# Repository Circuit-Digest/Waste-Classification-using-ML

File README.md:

# [Waste Classification Using Machine Learning and SCARA Robotic Arm](https://circuitdigest.com/videos/waste-classification-using-machine-learning-and-scara-robotic-arm)

Waste Classification Using Machine Learning and SCARA Robotic Arm
This project introduces an innovative solution to automate waste segregation using a SCARA Robot enhanced with computer vision and machine learning. The project used a pre-deployed AI model to classify the objects into organic or inorganic waste. At its core, the project utilises a Raspberry Pi paired with a USB camera to capture images of waste materials, this captured image is then processed with the help of inference SDK and the Roboflow waste classification API. Once classified, the robotic arm, controlled by an ESP32-C6 WROOM module, handles the waste, placing it into designated bins. This integration of robotics and artificial intelligence not only enhances automation but also contributes to effective waste management solutions.

The SCARA robot retains its compact and precise design, featuring NEMA 17 stepper motors powered by TMC2209 drivers for smooth operation, alongside SG90S servo motors for precise gripper control. The robust power system includes an LM2596-5 buck converter and an ADP7118AUJZ-3.3 LDO, ensuring the reliable operation of the ESP32-C6 and its peripherals. The Raspberry Pi handles image capture, and ML inferencing, leveraging the RoboFlow platform API for real-time inference. A Python-based control script on the Raspberry Pi seamlessly interfaces with the ESP32-C6 via serial communication to coordinate waste classification and robotic arm movements. This project exemplifies the potential of combining robotics and AI to solve real-world challenges. It provides a hands-on platform for exploring automation, embedded systems, and machine learning applications.

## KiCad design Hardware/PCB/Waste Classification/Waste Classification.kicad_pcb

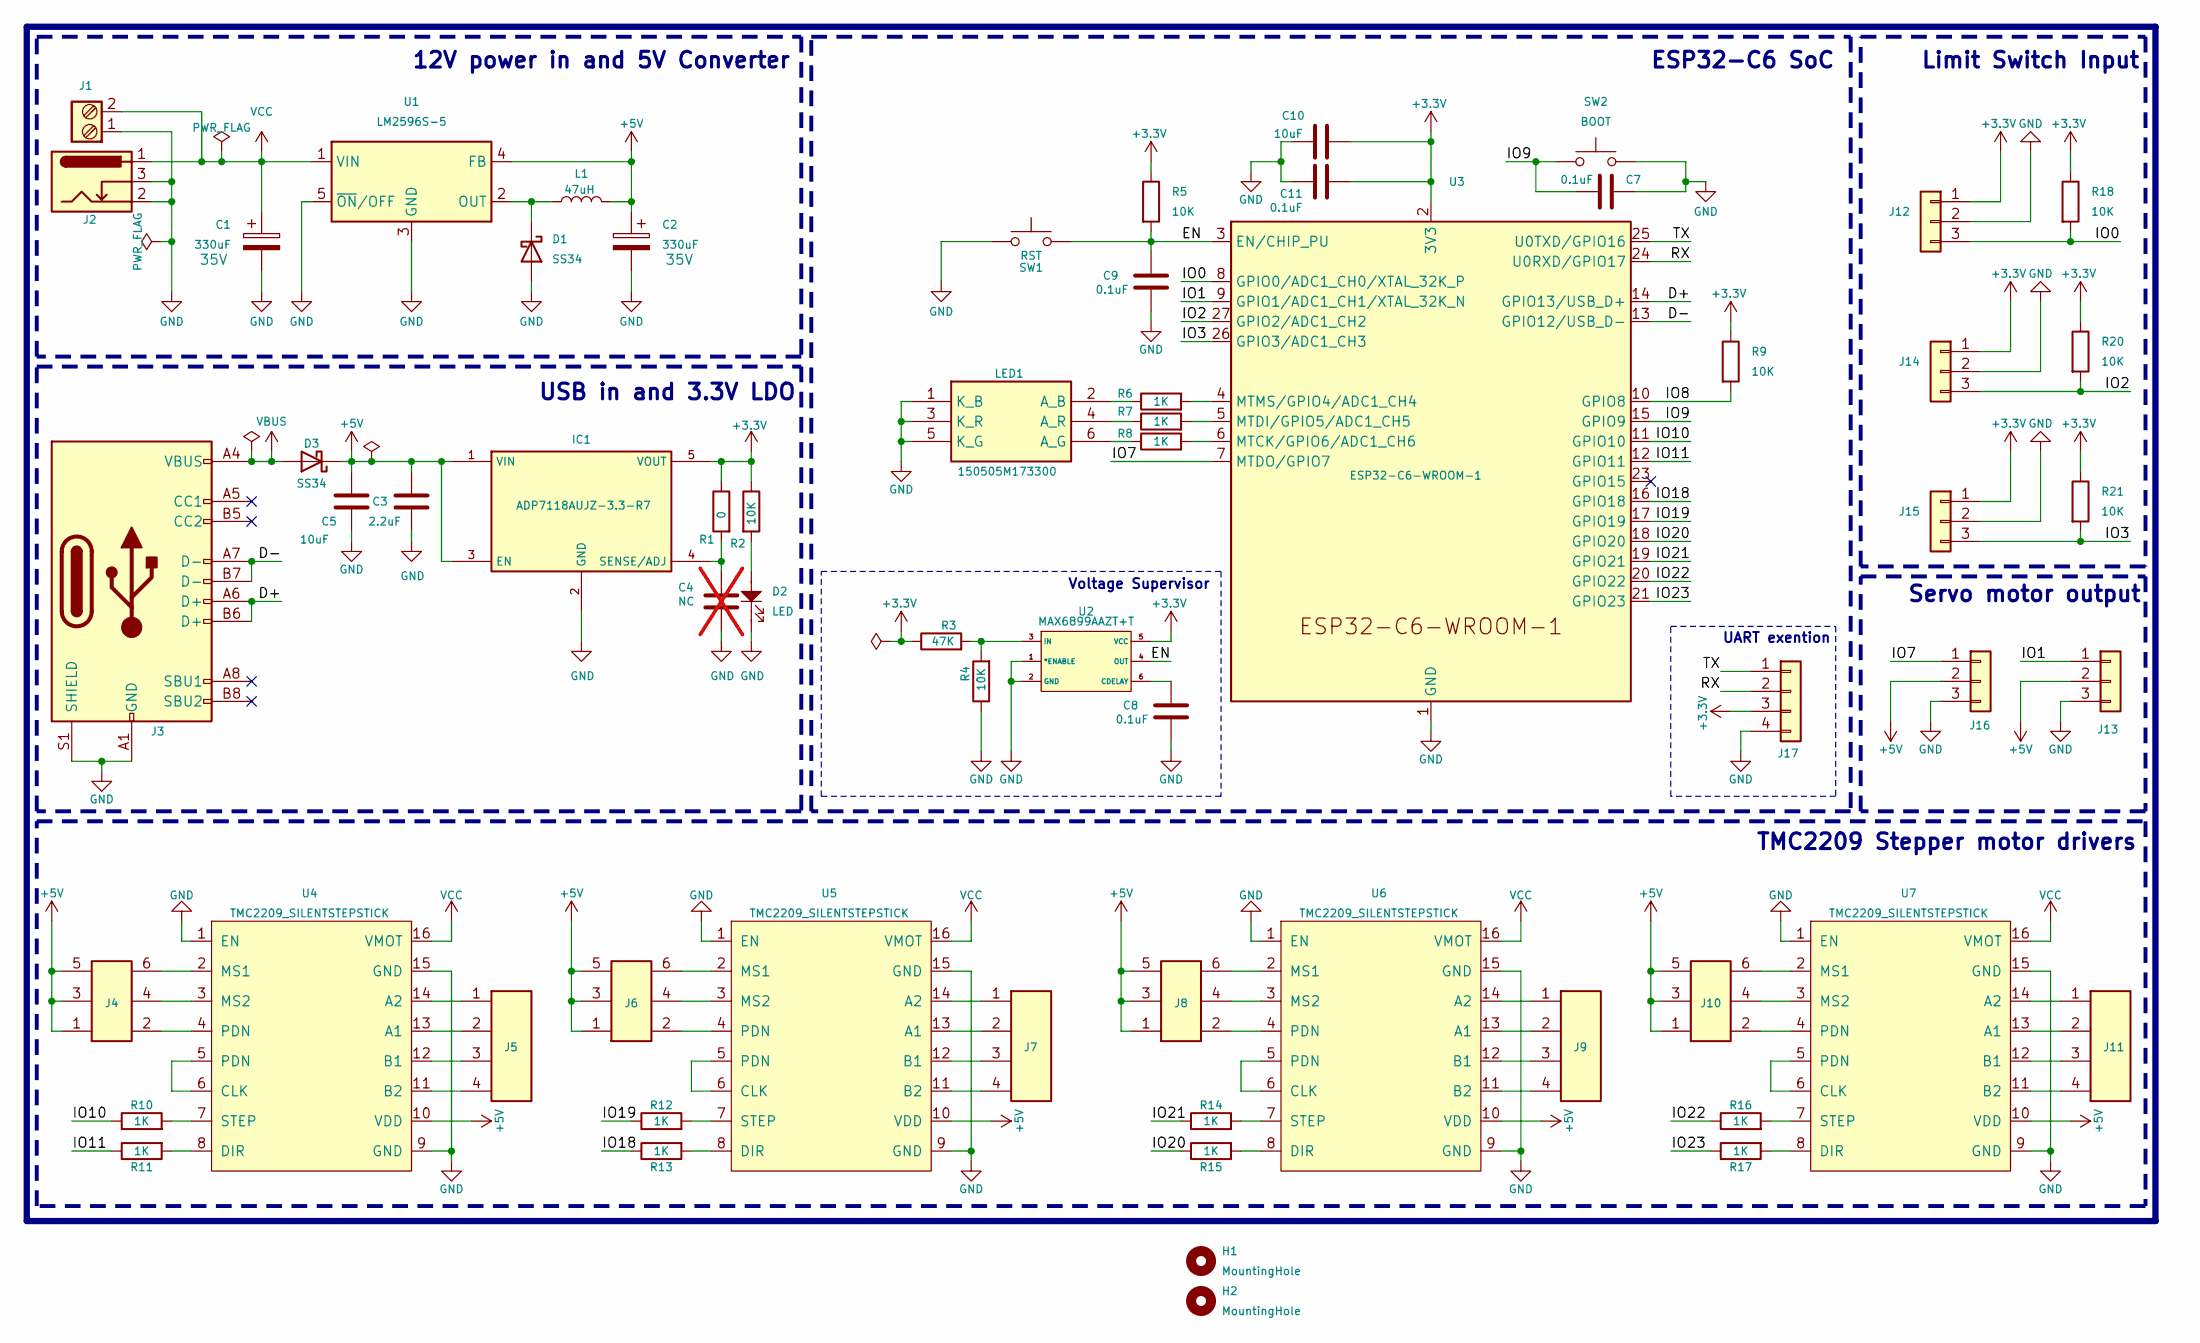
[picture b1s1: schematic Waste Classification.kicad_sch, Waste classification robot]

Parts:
C1, C2: 330uF; CAP_J-V_10X10P5_RUB; Voltage 35V
C3: 2.2uF; C_0603_1608Metric
C4: NC; C_0603_1608Metric; not fitted
C5, C10: 10uF; C_0805_2012Metric
C7, C8, C9, C11: 0.1uF; C_0603_1608Metric
D1, D3: SS34; D_SMA
D2: LED; LED_0805_2012Metric
H1, H2: MountingHole; MountingHole_2.2mm_M2_Pad
IC1: ADP7118AUJZ-3.3-R7; SOT95P280X100-5N; Mouser Part Number 584-ADP7118AUJZ3.3R7
J1: Screw_Terminal_2_P5.00mm; TerminalBlock_Phoenix_PT-1,5-2-5.0-H_1x02_P5.00mm_Horizontal
J2: Barrel_Jack_Switch; BarrelJack_Kycon_KLDX-0202-xC_Horizontal
J3: USB_C_Receptacle_USB2.0; USB_C_Receptacle_HRO_TYPE-C-31-M-12
J4, J6, J8, J10: Conn_02x03_Top_Bottom; PinHeader_2x03_P2.54mm_Vertical
J5, J7, J9, J11: Conn_01x04; JST_XH_B4B-XH-AM_1x04_P2.50mm_Vertical
J12, J13, J14, J15, J16: Conn_01x03; JST_XH_B3B-XH-AM_1x03_P2.50mm_Vertical
J17: Conn_01x04; JST_EH_B4B-EH-A_1x04_P2.50mm_Vertical
L1: 47uH; L_12x12mm_H8mm
LED1: 150505M173300; Mouser Part Number 710-150505M173300
R1: 0; R_0603_1608Metric
R2, R4, R5, R9, R18, R20, R21: 10K; R_0603_1608Metric
R3: 47K; R_0603_1608Metric
R6, R7, R8, R10, R11, R12, R13, R14, R15, R16, R17: 1K; R_0603_1608Metric
SW1: RST; Tactile 3x4x2mm TS-A010
SW2: BOOT; Tactile 3x4x2mm TS-A010
U1: LM2596S-5; TO-263-5_TabPin3
U2: MAX6899AAZT+T
U3: ESP32-C6-WROOM-1
U4, U5, U6, U7: TMC2209_SILENTSTEPSTICK; MODULE_TMC2209_SILENTSTEPSTICK

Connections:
+3.3V: C10.1, C11.1, IC1.5 (VOUT), J12.1, J14.1, J15.1, J17.3, R1.1, R2.1, R3.1, R5.1, R9.1, R18.1, R20.1, R21.1, U2.5 (VCC), U3.2 (3V3)
+5V: C2.1, C3.1, C5.1, D3.1 (K), IC1.1 (VIN), IC1.3 (EN), J4.1, J4.3, J4.5, J6.1, J6.3, J6.5, J8.1, J8.3, J8.5, J10.1, J10.3, J10.5, J13.2, J16.2, L1.2, U1.4 (FB), U4.10 (VDD), U5.10 (VDD), U6.10 (VDD), U7.10 (VDD)
/D+: J3.A6 (D+), J3.B6 (D+), U3.14 (GPIO13/USB_D+)
/D-: J3.A7 (D-), J3.B7 (D-), U3.13 (GPIO12/USB_D-)
/EN: C9.1, R5.2, SW1.2, U2.4 (OUT), U3.3 (EN/CHIP_PU)
/IO0: J12.3, R18.2, U3.8 (GPIO0/ADC1_CH0/XTAL_32K_P)
/IO1: J13.1, U3.9 (GPIO1/ADC1_CH1/XTAL_32K_N)
/IO2: J14.3, R20.2, U3.27 (GPIO2/ADC1_CH2)
/IO3: J15.3, R21.2, U3.26 (GPIO3/ADC1_CH3)
/IO7: J16.1, U3.7 (MTDO/GPIO7)
/IO8: R9.2, U3.10 (GPIO8)
/IO9: C7.2, SW2.2, U3.15 (GPIO9)
/IO10: R10.1, U3.11 (GPIO10)
/IO11: R11.1, U3.12 (GPIO11)
/IO18: R13.1, U3.16 (GPIO18)
/IO19: R12.1, U3.17 (GPIO19)
/IO20: R15.1, U3.18 (GPIO20)
/IO21: R14.1, U3.19 (GPIO21)
/IO22: R16.1, U3.20 (GPIO22)
/IO23: R17.1, U3.21 (GPIO23)
/RX: J17.2, U3.24 (U0RXD/GPIO17)
/TX: J17.1, U3.25 (U0TXD/GPIO16)
GND: C1.2, C2.2, C3.2, C4.2, C5.2, C7.1, C8.2, C9.2, C10.2, C11.2, D1.2 (A), D2.1, IC1.2 (GND), J1.1, J2.2, J2.3, J3.A1 (GND), J3.A12 (GND), J3.B1 (GND), J3.B12 (GND), J3.S1 (SHIELD), J12.2, J13.3, J14.2, J15.2, J16.3, J17.4, LED1.1 (K_B), LED1.3 (K_R), LED1.5 (K_G), R4.1, SW1.1, SW2.1, U1.3 (GND), U1.5 (~ON/OFF), U2.1 (*ENABLE), U2.2 (GND), U3.1 (GND), U3.28 (GND), U3.29 (GND), U4.1 (EN), U4.9 (GND), U4.15 (GND), U5.1 (EN), U5.9 (GND), U5.15 (GND), U6.1 (EN), U6.9 (GND), U6.15 (GND), U7.1 (EN), U7.9 (GND), U7.15 (GND)
unnamed: D1.1 (K), L1.1, U1.2 (OUT)
unnamed: D2.2, R2.2
unnamed: C4.1, IC1.4 (SENSE/ADJ), R1.2
unnamed: J4.2, U4.4 (PDN)
unnamed: J4.4, U4.3 (MS2)
unnamed: J4.6, U4.2 (MS1)
unnamed: J5.1, U4.14 (A2)
unnamed: J5.2, U4.13 (A1)
unnamed: J5.3, U4.12 (B1)
unnamed: J5.4, U4.11 (B2)
unnamed: J6.2, U5.4 (PDN)
unnamed: J6.4, U5.3 (MS2)
unnamed: J6.6, U5.2 (MS1)
unnamed: J7.1, U5.14 (A2)
unnamed: J7.2, U5.13 (A1)
unnamed: J7.3, U5.12 (B1)
unnamed: J7.4, U5.11 (B2)
unnamed: J8.2, U6.4 (PDN)
unnamed: J8.4, U6.3 (MS2)
unnamed: J8.6, U6.2 (MS1)
unnamed: J9.1, U6.14 (A2)
unnamed: J9.2, U6.13 (A1)
unnamed: J9.3, U6.12 (B1)
unnamed: J9.4, U6.11 (B2)
unnamed: J10.2, U7.4 (PDN)
unnamed: J10.4, U7.3 (MS2)
unnamed: J10.6, U7.2 (MS1)
unnamed: J11.1, U7.14 (A2)
unnamed: J11.2, U7.13 (A1)
unnamed: J11.3, U7.12 (B1)
unnamed: J11.4, U7.11 (B2)
unnamed: LED1.2 (A_B), R6.1
unnamed: LED1.6 (A_G), R8.1
unnamed: LED1.4 (A_R), R7.1
unnamed: C8.1, U2.6 (CDELAY)
unnamed: R3.2, R4.2, U2.3 (IN)
unnamed: R8.2, U3.6 (MTCK/GPIO6/ADC1_CH6)
unnamed: R7.2, U3.5 (MTDI/GPIO5/ADC1_CH5)
unnamed: R6.2, U3.4 (MTMS/GPIO4/ADC1_CH4)
unnamed: U4.5 (PDN), U4.6 (CLK)
unnamed: R11.2, U4.8 (DIR)
unnamed: R10.2, U4.7 (STEP)
unnamed: U5.5 (PDN), U5.6 (CLK)
unnamed: R13.2, U5.8 (DIR)
unnamed: R12.2, U5.7 (STEP)
unnamed: U6.5 (PDN), U6.6 (CLK)
unnamed: R15.2, U6.8 (DIR)
unnamed: R14.2, U6.7 (STEP)
unnamed: U7.5 (PDN), U7.6 (CLK)
unnamed: R17.2, U7.8 (DIR)
unnamed: R16.2, U7.7 (STEP)
VBUS: D3.2 (A), J3.A4 (VBUS), J3.A9 (VBUS), J3.B4 (VBUS), J3.B9 (VBUS)
VCC: C1.1, J1.2, J2.1, U1.1 (VIN), U4.16 (VMOT), U5.16 (VMOT), U6.16 (VMOT), U7.16 (VMOT)

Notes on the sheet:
USB in and 3.3V LDO
UART exention
TMC2209 Stepper motor drivers
ESP32-C6 SoC
Voltage Supervisor
12V power in and 5V Converter
Servo motor output
Limit Switch Input

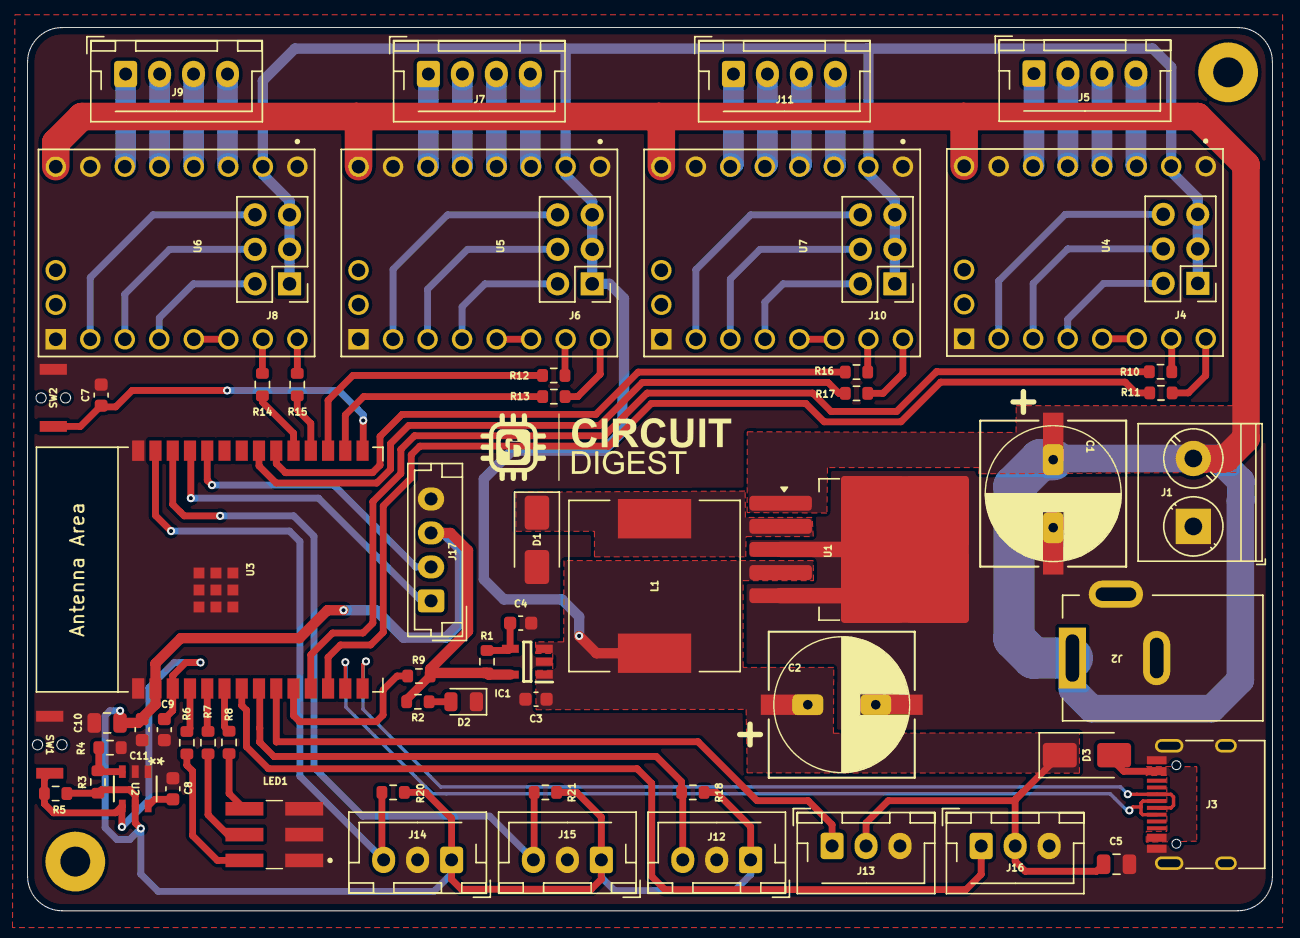
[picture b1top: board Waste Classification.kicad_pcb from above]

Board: 2 copper layers, 91.6 x 65.0 mm, 64 parts (0 on the bottom side), 76 nets.
